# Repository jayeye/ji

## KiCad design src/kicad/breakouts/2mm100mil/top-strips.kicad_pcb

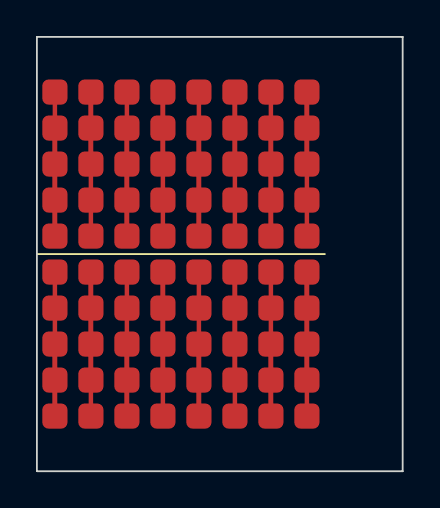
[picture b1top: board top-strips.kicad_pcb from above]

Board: 2 copper layers, 20.3 x 24.1 mm, 16 parts (0 on the bottom side), 16 nets.

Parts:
S1, S2, S3, S4, S5, S6, S7, S8, S9, S10, S11, S12, S13, S14, S15, S16: Conn_01x05; smd1mm4pad-quint

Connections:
/B1: S9.1, S9.2, S9.3, S9.4, S9.5
/B2: S10.1, S10.2, S10.3, S10.4, S10.5
/B3: S11.1, S11.2, S11.3, S11.4, S11.5
/B4: S12.1, S12.2, S12.3, S12.4, S12.5
/B5: S13.1, S13.2, S13.3, S13.4, S13.5
/B6: S14.1, S14.2, S14.3, S14.4, S14.5
/B7: S15.1, S15.2, S15.3, S15.4, S15.5
/B8: S16.1, S16.2, S16.3, S16.4, S16.5
/T1: S1.1, S1.2, S1.3, S1.4, S1.5
/T2: S2.1, S2.2, S2.3, S2.4, S2.5
/T3: S3.1, S3.2, S3.3, S3.4, S3.5
/T4: S4.1, S4.2, S4.3, S4.4, S4.5
/T5: S5.1, S5.2, S5.3, S5.4, S5.5
/T6: S6.1, S6.2, S6.3, S6.4, S6.5
/T7: S7.1, S7.2, S7.3, S7.4, S7.5
/T8: S8.1, S8.2, S8.3, S8.4, S8.5

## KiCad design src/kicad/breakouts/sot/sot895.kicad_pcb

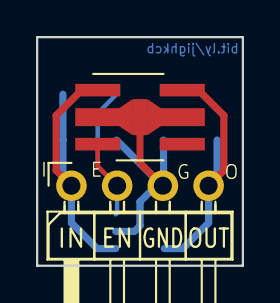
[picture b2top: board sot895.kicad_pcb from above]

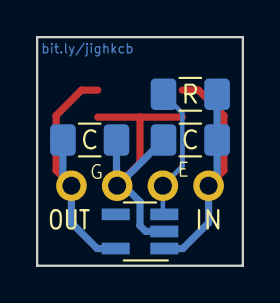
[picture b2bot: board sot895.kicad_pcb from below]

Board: 2 copper layers, 11.4 x 12.7 mm, 6 parts (4 on the bottom side), 4 nets.

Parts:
C1, C2: CP; C_1206_3216Metric_Pad1.42x1.75mm_HandSolder
J17: Conn_01x04_Male; PinHeader_1x04_P2.54mm_Horizontal_Left
R11: R; R_1206_3216Metric_Pad1.42x1.75mm_HandSolder
U1: AP2112K-3.3 SOT-89-5; SOT-89-5_Handsoldering
U2: AP2112K-3.3 SOT-25; SOT-23-5_HandSoldering

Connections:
unnamed: C1.1, J17.1, R11.1, U1.1, U2.1
unnamed: C1.2, C2.2, J17.3, U1.2, U2.2
unnamed: C2.1, J17.4, U1.5, U2.5
unnamed: J17.2, R11.2, U1.3, U2.3

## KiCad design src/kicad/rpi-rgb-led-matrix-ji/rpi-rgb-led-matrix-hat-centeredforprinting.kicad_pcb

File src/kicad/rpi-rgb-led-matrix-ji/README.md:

This is a reworking of [https://github.com/hzeller/rpi-rgb-led-matrix/tree/master/adapter](https://github.com/hzeller/rpi-rgb-led-matrix/tree/master/adapter).

* Both versions will work on both a _zero_ and an ordinary RPi.
  - Some 64-row panels have a fifth address pin, labeled **E**, either
    at pin 4 or pin 8. Use the corresponding solder jumper to
    accommodate those panels. Obviously, you cannot mix 32- and 64-row
    panels on the same chain.
* The _zero_ version is meant to be plugged into an RPi Zero/ZeroW and
  then the whole thing plugged directly into the HUB75
  connector. Obviously only the middle 16 pins are used, but the
  20-pin header makes it a lot easier to properly center it.
* The _hat_ version can be built without the ID EEPROM (only then it cannot be called a HAT!).
  - Do not install R4/R5/R6/U5 if you do not care about the ID EEPROM functionality.
* The _hat_ version can be built without the virtual diode (again, it cannot be called a HAT then).
  - Use **ONLY ONE** power source; either the same PSU powering the LED matrices or the microUSB powering the Pi, **BUT NOT BOTH**.
  - Do not install J3/Q1/Q2/R2/R3
  - Short pads 5 and 6 of Q2 with a blob of solder.

The pictures are from the first version of the circuit: the virtual diode circuitry was slightly wrong (not an issue when powering from J3) and the EEPROM was missing the bypass capacitor.

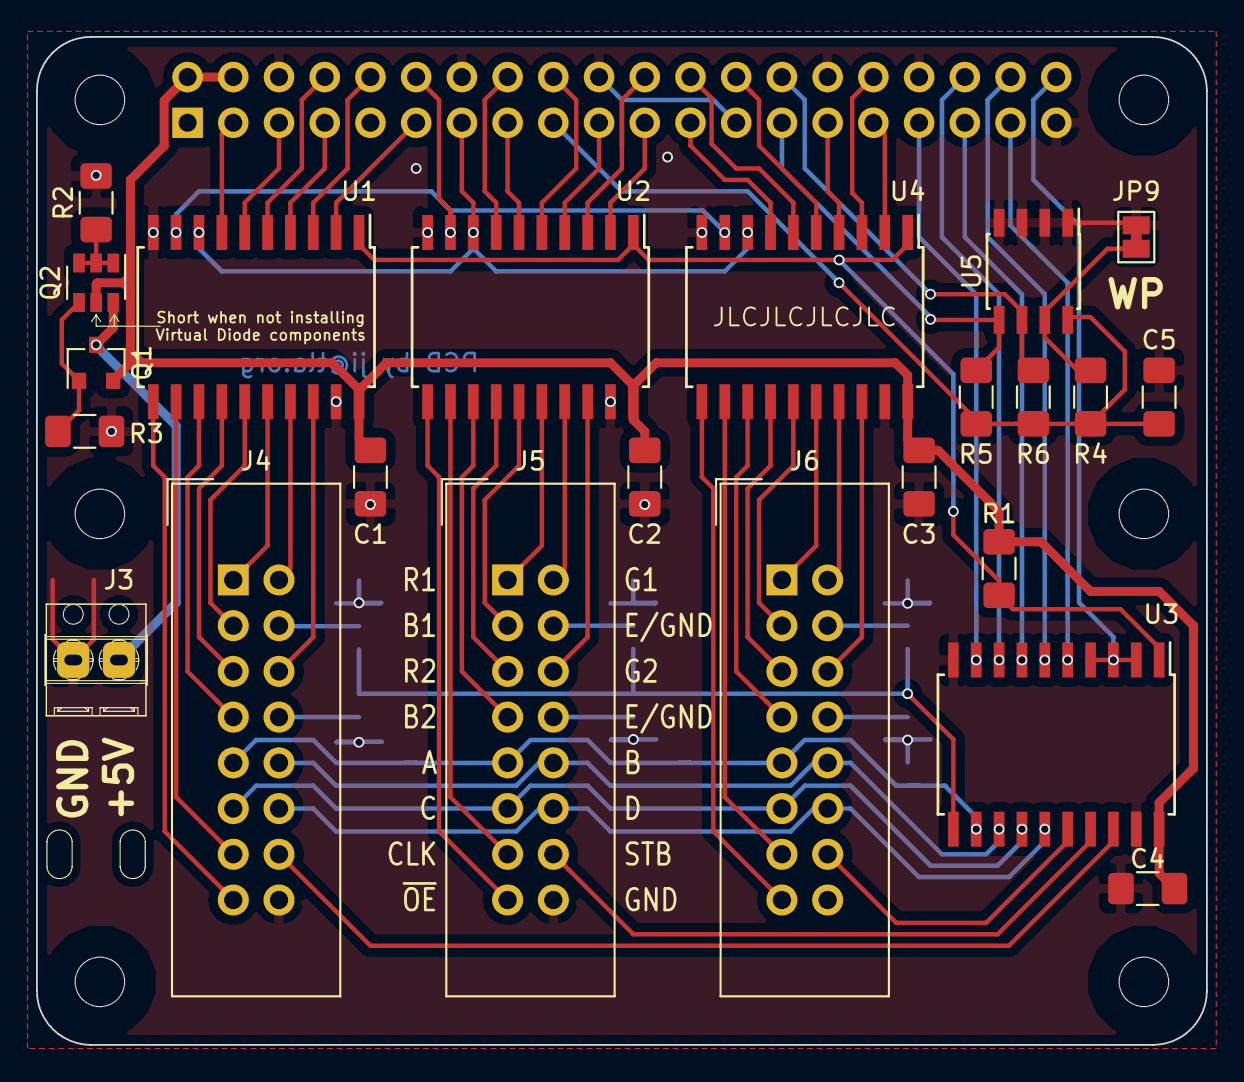
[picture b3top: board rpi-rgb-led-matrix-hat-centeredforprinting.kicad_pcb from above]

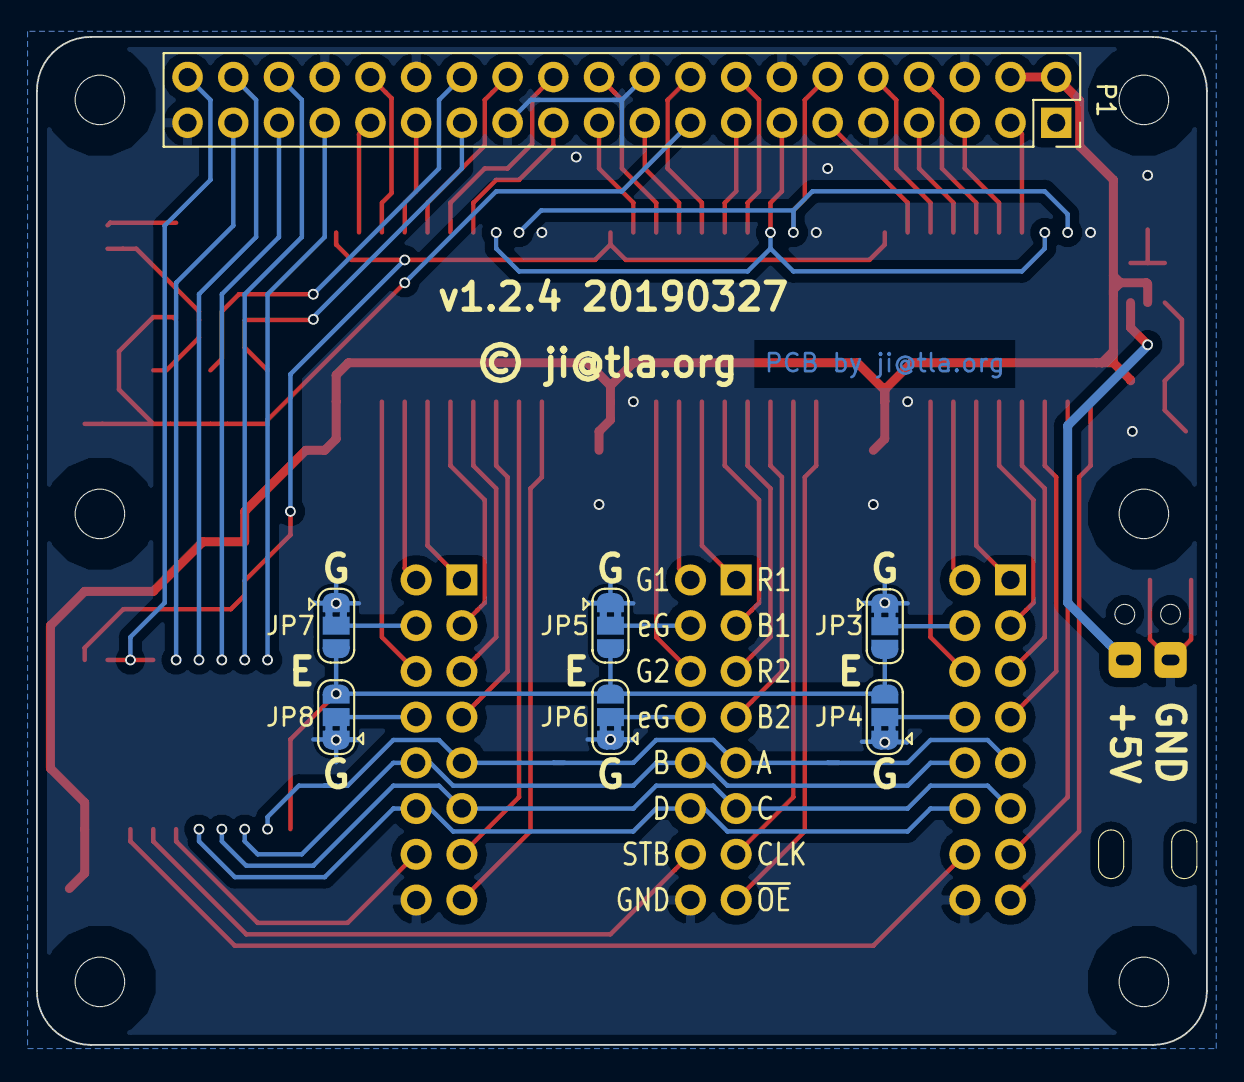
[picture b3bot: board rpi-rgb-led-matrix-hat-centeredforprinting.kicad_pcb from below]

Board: 2 copper layers, 65.0 x 56.0 mm, 38 parts (7 on the bottom side), 74 nets.

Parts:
C1, C2, C3, C4, C5: 100nF; C_1206_3216Metric_Pad1.42x1.75mm_HandSolder
H1, H2, H3, H4, H5, H6: MountingHole; RPi_Hat_Mounting_Hole
H7, H8: Power cable tie-down; tiedown
J3: Screw_Terminal_01x02; PhoenixMPT02
J4, J5, J6: Conn_02x08_Odd_Even; IDC-Header_2x08_P2.54mm_Vertical
JP3, JP4, JP5, JP6, JP7, JP8: SolderJumper_3_Bridged12; SolderJumper-3_P1.3mm_Bridged2Bar12_RoundedPad1.0x1.5mm
JP9: SolderJumper_2_Bridged; SolderJumper-2_P1.3mm_Bridged_Pad1.0x1.5mm
P1: Raspberry_Pi_2_3; PinSocket_2x20_P2.54mm_Vertical
Q1: DMG2305UX; SOT-23
Q2: DMMT5401; SOT-23-6
R1, R2, R4: 10K; R_1206_3216Metric_Pad1.42x1.75mm_HandSolder
R3: 47K; R_1206_3216Metric_Pad1.42x1.75mm_HandSolder
R5, R6: 3K9; R_1206_3216Metric_Pad1.42x1.75mm_HandSolder
U1, U2, U3, U4: 74HCT245; SOIC-20W_7.5x12.8mm_P1.27mm
U5: CAT24C32; SOIC-8_3.9x4.9mm_P1.27mm

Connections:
+3V3: C5.1, P1.17, R4.1, R5.1, R6.1, U5.8
+5V: C1.1, C2.1, C3.1, C4.1, P1.2, P1.4, Q1.2, Q2.5, R1.1, U1.20, U2.20, U3.20, U4.20
+5VP: J3.1, Q1.3, Q2.6
/A: P1.36, U3.8
/A_R: J4.9, J5.9, J6.9, U3.12
/B: P1.35, U3.7
/B1_1: P1.8, U1.5
/B1_1_R: J4.3, U1.15
/B1_2: P1.18, U2.5
/B1_2_R: J5.3, U2.15
/B1_3: P1.26, U4.5
/B1_3_R: J6.3, U4.15
/B2_1: P1.3, U1.7
/B2_1_R: J4.7, U1.13
/B2_2: P1.16, U2.7
/B2_2_R: J5.7, U2.13
/B2_3: P1.23, U4.7
/B2_3_R: J6.7, U4.13
/B_R: J4.10, J5.10, J6.10, U3.13
/C: P1.38, U3.6
/CLK: P1.13, U1.8, U2.8, U4.8
/CLK_1_R: J4.13, U1.12
/CLK_2_R: J5.13, U2.12
/CLK_3_R: J6.13, U4.12
/C_R: J4.11, J5.11, J6.11, U3.14
/D: P1.37, U3.5
/D_R: J4.12, J5.12, J6.12, U3.15
/E: P1.33, U3.9
/E_R: JP3.3, JP4.3, JP5.3, JP6.3, JP7.3, JP8.3, U3.11
/G1_1: P1.10, U1.3
/G1_1_R: J4.2, U1.17
/G1_2: P1.22, U2.3
/G1_2_R: J5.2, U2.17
/G1_3: P1.32, U4.3
/G1_3_R: J6.2, U4.17
/G2_1: P1.11, U1.2
/G2_1_R: J4.6, U1.18
/G2_2: P1.21, U2.2
/G2_2_R: J5.6, U2.18
/G2_3: P1.31, U4.2
/G2_3_R: J6.6, U4.18
/ID_SC: P1.28, R6.2, U5.6
/ID_SD: P1.27, R5.2, U5.5
/R1_1: P1.7, U1.4
/R1_1_R: J4.1, U1.16
/R1_2: P1.19, U2.4
/R1_2_R: J5.1, U2.16
/R1_3: P1.29, U4.4
/R1_3_R: J6.1, U4.16
/R2_1: P1.5, U1.6
/R2_1_R: J4.5, U1.14
/R2_2: P1.15, U2.6
/R2_2_R: J5.5, U2.14
/R2_3: P1.24, U4.6
/R2_3_R: J6.5, U4.14
/STROBE: P1.40, U3.2, U3.3, U3.4
/STROBE_1_R: J4.14, U3.18
/STROBE_2_R: J5.14, U3.17
/STROBE_3_R: J6.14, U3.16
/~OE: P1.12, U1.9, U2.9, U4.9
/~OE_1_R: J4.15, U1.11
/~OE_2_R: J5.15, U2.11
/~OE_3_R: J6.15, U4.11
GND: C1.2, C2.2, C3.2, C4.2, C5.2, J3.2, J4.16, J5.16, J6.16, JP3.1, JP4.1, JP5.1, JP6.1, JP7.1, JP8.1, JP9.2, P1.6, P1.9, P1.14, P1.20, P1.25, P1.30, P1.34, P1.39, R2.2, R3.2, U1.10, U1.19, U2.10, U2.19, U3.10, U3.19, U4.10, U4.19, U5.1, U5.2, U5.3, U5.4
unnamed: J4.4, JP3.2
unnamed: J4.8, JP4.2
unnamed: J5.4, JP5.2
unnamed: J5.8, JP6.2
unnamed: J6.4, JP7.2
unnamed: J6.8, JP8.2
unnamed: JP9.1, R4.2, U5.7
unnamed: Q1.1, Q2.4, R3.1
unnamed: Q2.1, Q2.2, Q2.3, R2.1
unnamed: R1.2, U1.1, U2.1, U3.1, U4.1

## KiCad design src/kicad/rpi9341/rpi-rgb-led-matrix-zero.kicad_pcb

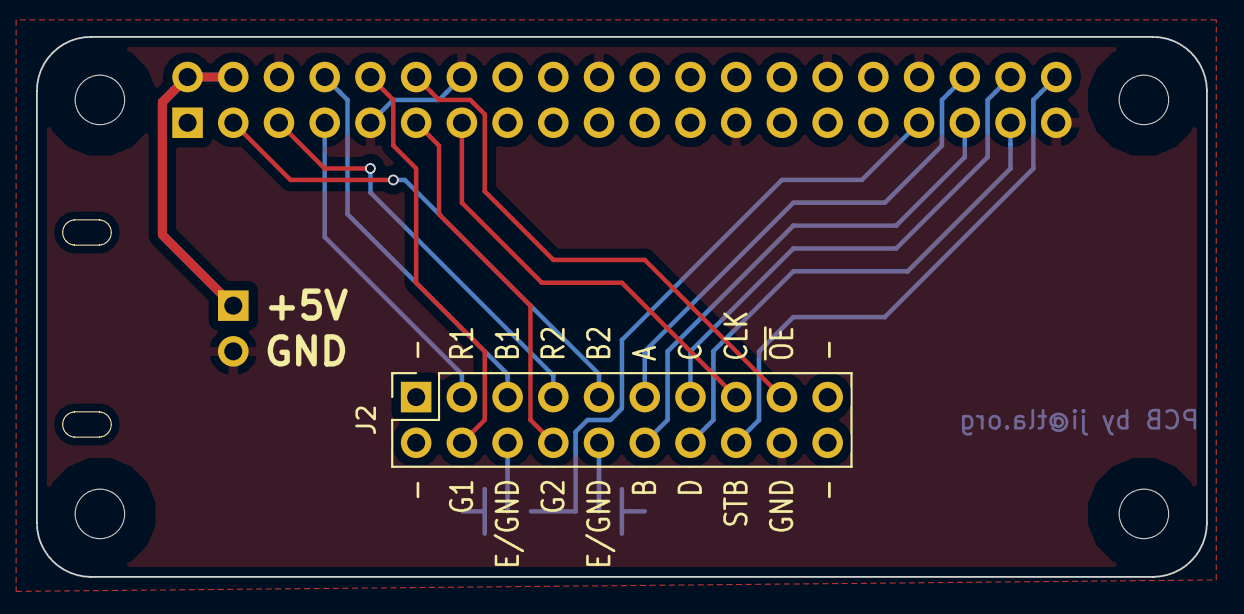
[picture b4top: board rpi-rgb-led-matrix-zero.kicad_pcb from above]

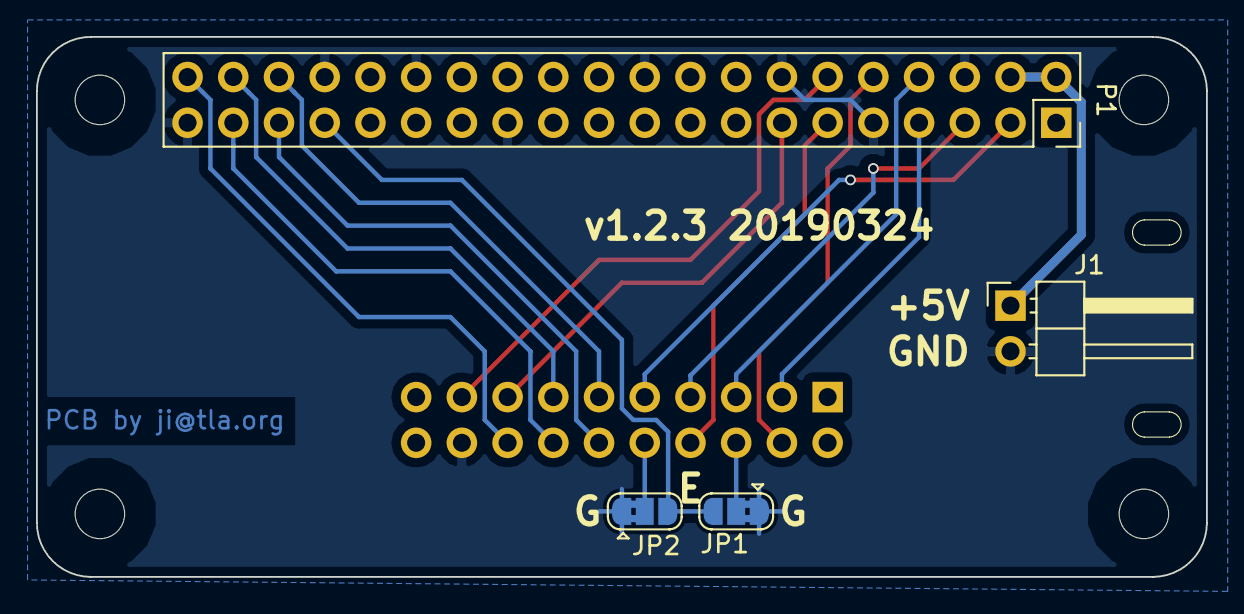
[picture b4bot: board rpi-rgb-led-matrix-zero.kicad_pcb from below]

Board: 2 copper layers, 65.0 x 30.0 mm, 7 parts (4 on the bottom side), 18 nets.

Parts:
H1, H2: MountingHole; tiedown
J1: Conn_01x02_Male; PinHeader_1x02_P2.54mm_Horizontal
J2: Conn_02x10_Odd_Even; PinSocket_2x10_P2.54mm_Vertical
JP1, JP2: SolderJumper_3_Bridged12; SolderJumper-3_P1.3mm_Bridged2Bar12_RoundedPad1.0x1.5mm
P1: Raspberry_Pi_2_3; PinSocket_2x20_P2.54mm_Vertical

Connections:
/A: J2.11, P1.36
/B: J2.12, P1.35
/B1_1: J2.5, P1.8
/B2_1: J2.9, P1.3
/C: J2.13, P1.38
/CLK: J2.15, P1.13
/D: J2.14, P1.37
/E: JP1.3, JP2.3, P1.33
/G1_1: J2.4, P1.10
/G2_1: J2.8, P1.11
/HAT_5V: J1.1, P1.2, P1.4
/R1_1: J2.3, P1.7
/R2_1: J2.7, P1.5
/STROBE: J2.16, P1.40
/~OE: J2.17, P1.12
GND: J1.2, J2.18, JP1.1, JP2.1, P1.6, P1.9, P1.14, P1.20, P1.25, P1.30, P1.34, P1.39
unnamed: J2.6, JP1.2
unnamed: J2.10, JP2.2

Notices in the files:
src/kicad/rpi-rgb-led-matrix-ji/rpi-rgb-led-matrix-hat-centeredforprinting.kicad_pcb:
Creative Commons Attribution Required
© ji@tla.org
